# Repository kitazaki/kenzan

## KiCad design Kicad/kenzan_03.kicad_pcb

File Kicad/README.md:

|項目|個数|入手先（日本国内）||
|---|---|---|---|
|基板（ガーバーファイル）| 1 | | https://github.com/kitazaki/kenzan/tree/master/Kicad
|チップ抵抗（330Ω）| 9 | 千石電商　KOA RK73B2ATTD331J 2012(0805)チップ抵抗 330Ω | マルツ【RK73H1JTTD331F】RK73H 330Ω 0.125W ±1%
|ピンヘッダ（メス2ピン）| 18 | 秋月電子 [FH-1x2SG/RH] ピンソケット（メス）　１×２（２Ｐ）| 千石電商 114-002 PCBソケット 1列×2P (ストレート・標準ピッチ) |
|ピンヘッダ（ストレート8ピン）| 1 |秋月電子　ピンヘッダ　１×４０　（４０Ｐ）[PH-1x40SG]	|千石電商　2544-1×40 11.8(6.3/3.0) ピンヘッダ 1列×40P (ストレート・標準ピッチ)
|ピンヘッダ（ストレート6ピン）| 2 | ↑ | ↑ |

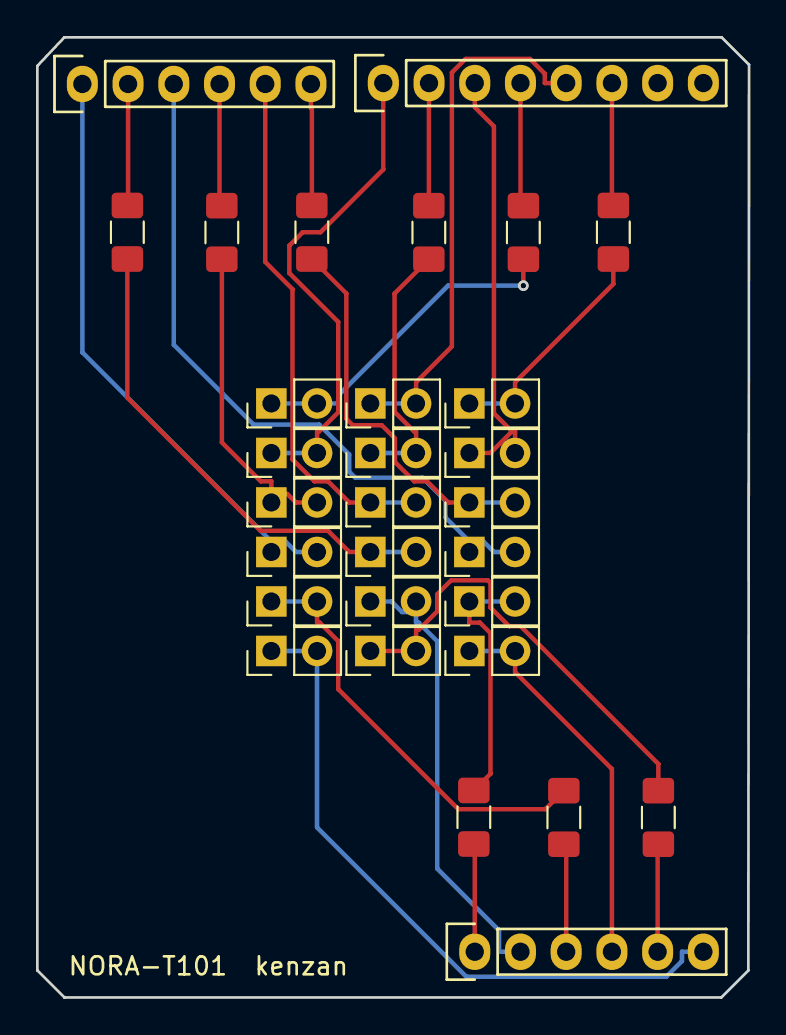
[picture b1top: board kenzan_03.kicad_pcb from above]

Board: 2 copper layers, 39.5 x 53.3 mm, 30 parts (0 on the bottom side), 27 nets.

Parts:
J1, J2, J3, J4, J5, J6, J7, J8, J9, J10, J11, J12, J13, J14, J15, J16, J17, J18: Conn_01x02_Female; PinHeader_1x02_P2.54mm_Vertical
P1: Digital; Socket_Strip_Arduino_1x06
P2: Analog; Socket_Strip_Arduino_1x06
P4: Digital; Socket_Strip_Arduino_1x08
R1, R2, R3, R4, R5, R6, R7, R8, R9: R; R_1206_3216Metric_Pad1.42x1.75mm_HandSolder

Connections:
/G2: P4.6, R1.2
/G3: J2.1, J2.2, P4.5
/G4: P4.4, R2.2
/G5: J4.1, J4.2, P4.3
/G6: P4.2, R3.2
/G7: J6.1, J6.2, P4.1
/G8: P1.6, R4.2
/G9: J8.1, J8.2, P1.5
/G10: P1.4, R5.2
/G11: J10.1, J10.2, P1.3
/G12: P1.2, R6.2
/G13: J12.1, J12.2, P1.1
/G14: P2.1, R7.1
/G15: J14.1, J14.2, P2.2
/G16: P2.3, R8.1
/G17: J16.1, J16.2, P2.4
/G18: P2.5, R9.1
/G19: J18.1, J18.2, P2.6
unnamed: J1.1, J1.2, R1.1
unnamed: J3.1, J3.2, R2.1
unnamed: J5.1, J5.2, R3.1
unnamed: J7.1, J7.2, R4.1
unnamed: J9.1, J9.2, R5.1
unnamed: J11.1, J11.2, R6.1
unnamed: J13.1, J13.2, R7.2
unnamed: J15.1, J15.2, R8.2
unnamed: J17.1, J17.2, R9.2
